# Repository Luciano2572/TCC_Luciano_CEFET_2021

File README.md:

# TCC_Luciano_CEFET_2021
Arquivos do projeto executado para o trabalho de conclusão de curso para o curso de engenharia eletrônica, Profa. Orientadora: Milena Faria Pinto, D.Sc.

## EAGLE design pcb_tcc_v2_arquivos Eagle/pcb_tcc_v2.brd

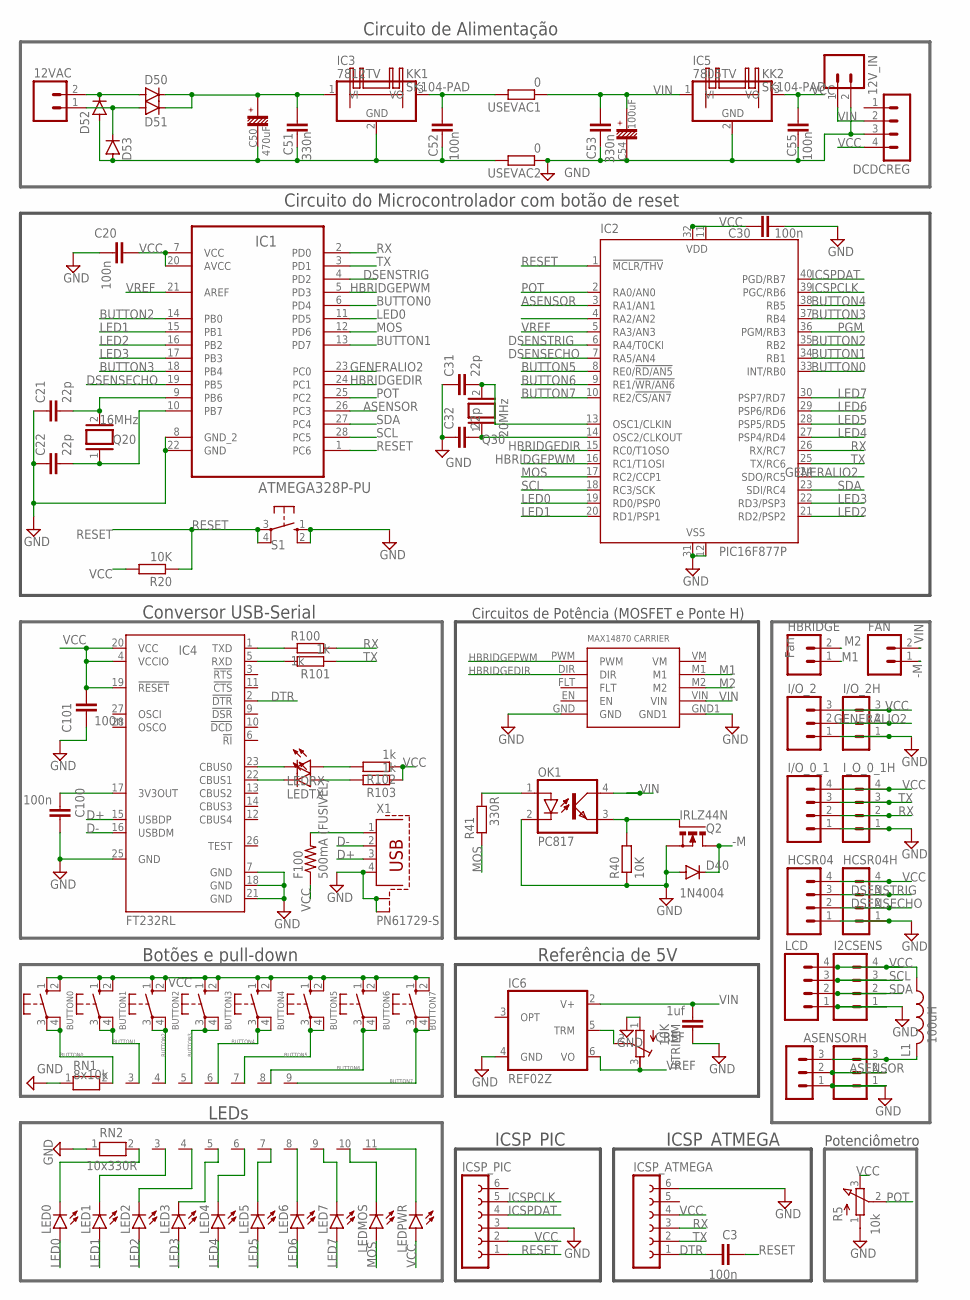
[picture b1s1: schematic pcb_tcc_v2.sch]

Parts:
12VAC, 12V_IN: M02; 02P
ASENSOR: M03; 03P
ASENSORH: MA03-1
BUTTON0, BUTTON1, BUTTON2, BUTTON3, BUTTON4, BUTTON5, BUTTON6, BUTTON7: 10-XX; B3F-10XX
C3, C20, C30, C52, C55, C100, C101: 100n; C5B2.5
C21, C22, C31, C32: 22p; C5B2.5
C50: 470uF; 16V-10-5.08
C51, C53: 330n; C5B2.5
C54: 100uF; 16V-6.3-2.54
CREF: 1uf; C2.5-2
D40, D50, D51, D52, D53: 1N4004; DO41-10
DCDCREG: MA04-1
F100: 500mA (FUSIVEL); R1206
FAN: M02; 02P
HBRIDGE: M02; 02P
HCSR04: M04; 04P
HCSR04H: MA04-1
I2CSENS: M04; 04P
I/O_0_1: M04; 04P
I/O_2: M03; 03P
I/O_2H: MA03-1
IC1: ATMEGA328P-PU; DIP254P762X457-28
IC2: PIC16F877P; DIL40
IC3: 7812TV; TO220V
IC4: FT232RL; SSOP28
IC5: 7805TV; TO220V
IC6: REF02Z; DIL08
ICSP_ATMEGA: FE06-1; FE06
ICSP_PIC: FE06-1; FE06
I_O_0_1H: MA04-1
KK1, KK2: SK104-PAD
L1: 100uH; 0204/7
LCD: M04; 04P
LED0, LED1, LED2, LED3, LED4, LED5, LED6, LED7: LED3MM
LEDMOS: LED3MM
LEDPWR: LED3MM
LEDRX: LED3MM
LEDTX: LED3MM
OK1: PC817; DIL04
Q2: IRLZ44N; TO220BV
Q20: 16MHz; QS
Q30: 20MHz; QS
R5: 10k; 3RP/1610N
R20, R40: 10K; 0207/10
R41: 330R; 0207/7
R100, R101, R102, R103: 1k; 0207/10
RN1: 8x10k; RN-9
RN2: 10x330R; RN-11
RTRIMM: 10K; RTRIM3296W
S1: 10-XX; B3F-10XX
U$1: MAX14870; POLOLU_CARRIER
USEVAC1, USEVAC2: 0; 0207/10
X1: PN61729-S

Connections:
-M: D40.C, FAN.1, Q2.D
ASENSOR: ASENSOR.2, ASENSORH.2, IC1.26 (PC3), IC2.3 (RA1/AN1)
BUTTON0: BUTTON0.3, BUTTON0.4 (P1), IC1.6 (PD4), IC2.33 (INT/RB0), RN1.2
BUTTON1: BUTTON1.3, BUTTON1.4 (P1), IC1.13 (PD7), IC2.34 (RB1), RN1.3
BUTTON2: BUTTON2.3, BUTTON2.4 (P1), IC1.14 (PB0), IC2.35 (RB2), RN1.4
BUTTON3: BUTTON3.3, BUTTON3.4 (P1), IC1.18 (PB4), IC2.37 (RB4), RN1.5
BUTTON4: BUTTON4.3, BUTTON4.4 (P1), IC2.38 (RB5), RN1.6
BUTTON5: BUTTON5.3, BUTTON5.4 (P1), IC2.8 (RE0/!RD/AN5), RN1.7
BUTTON6: BUTTON6.3, BUTTON6.4 (P1), IC2.9 (RE1/!WR/AN6), RN1.8
BUTTON7: BUTTON7.3, BUTTON7.4 (P1), IC2.10 (RE2/!CS/AN7), RN1.9
D+: IC4.15 (USBDP), X1.3
D-: IC4.16 (USBDM), X1.2
DSENSECHO: HCSR04.2, HCSR04H.2, IC1.19 (PB5), IC2.7 (RA5/AN4)
DSENSTRIG: HCSR04.3, HCSR04H.3, IC1.4 (PD2), IC2.6 (RA4/T0CKI)
DTR: C3.1, IC4.2 (!DTR), ICSP_ATMEGA.1
GENERALIO2: I/O_2.2, I/O_2H.2, IC1.23 (PC0), IC2.24 (SDO/RC5)
GND: 12V_IN.2, ASENSOR.1, ASENSORH.1, C20.2, C21.1, C22.1, C30.2, C31.1, C32.1, C53.1, C54.-, C55.1, C100.1, C101.2, CREF.1, D40.A, DCDCREG.3, HCSR04.1, HCSR04H.1, I2CSENS.1, I/O_0_1.1, I/O_2.1, I/O_2H.1, IC1.8 (GND_2), IC1.22 (GND), IC2.12 (VSS), IC2.31 (VSS), IC4.7 (GND), IC4.18 (GND), IC4.21 (GND), IC4.25 (GND), IC5.2 (GND), IC6.4 (GND), ICSP_ATMEGA.6, ICSP_PIC.3, I_O_0_1H.1, LCD.1, OK1.2 (C), Q2.S, R5.1 (A), R40.1, RN1.1, RN2.1, RTRIMM.1 (A), S1.1 (S), S1.2 (S1), U$1.GND, U$1.GND1, USEVAC2.1, X1.4, X1.S1, X1.S2
HBRIDGEDIR: IC1.24 (PC1), IC2.15 (RC0/T1OSO), U$1.DIR
HBRIDGEPWM: IC1.5 (PD3), IC2.16 (RC1/T1OSI), U$1.PWM
ICSPCLK: IC2.39 (PGC/RB6), ICSP_PIC.5
ICSPDAT: IC2.40 (PGD/RB7), ICSP_PIC.4
LED0: IC1.11 (PD5), IC2.19 (RD0/PSP0), LED0.A
LED1: IC1.15 (PB1), IC2.20 (RD1/PSP1), LED1.A
LED2: IC1.16 (PB2), IC2.21 (RD2/PSP2), LED2.A
LED3: IC1.17 (PB3), IC2.22 (RD3/PSP3), LED3.A
LED4: IC2.27 (PSP4/RD4), LED4.A
LED5: IC2.28 (PSP5/RD5), LED5.A
LED6: IC2.29 (PSP6/RD6), LED6.A
LED7: IC2.30 (PSP7/RD7), LED7.A
M1: HBRIDGE.1, U$1.M1
M2: HBRIDGE.2, U$1.M2
MOS: IC1.12 (PD6), IC2.17 (RC2/CCP1), LEDMOS.A, R41.1
unnamed: C21.2, IC1.9 (PB6), Q20.2
unnamed: C22.2, IC1.10 (PB7), Q20.1
unnamed: 12VAC.2, D50.A, D52.C
unnamed: OK1.3 (EMIT), Q2.G, R40.2
unnamed: 12VAC.1, D51.A, D53.C
unnamed: ASENSOR.3, ASENSORH.3, L1.2
unnamed: C50.-, C51.1, C52.1, D52.A, D53.A, IC3.2 (GND), USEVAC2.2
unnamed: OK1.1 (A), R41.2
unnamed: C50.+, C51.2, D50.C, D51.C, IC3.1 (VI)
unnamed: LED0.K (C), RN2.2
unnamed: C100.2, IC4.17 (3V3OUT)
unnamed: IC4.1 (TXD), R100.1
unnamed: IC4.5 (RXD), R101.2
unnamed: C52.2, IC3.3 (VO), USEVAC1.2
unnamed: LED1.K (C), RN2.3
unnamed: LED2.K (C), RN2.4
unnamed: LED3.K (C), RN2.5
unnamed: LED4.K (C), RN2.6
unnamed: LED5.K (C), RN2.7
unnamed: C31.2, IC2.13 (OSC1/CLKIN), Q30.2
unnamed: C32.2, IC2.14 (OSC2/CLKOUT), Q30.1
unnamed: LED6.K (C), RN2.8
unnamed: LED7.K (C), RN2.9
unnamed: LEDMOS.K (C), RN2.10
unnamed: IC6.5 (TRM), RTRIMM.2 (S)
unnamed: LEDPWR.K (C), RN2.11
unnamed: F100.2, X1.1
unnamed: IC4.23 (CBUS0), LEDRX.K (C)
unnamed: IC4.22 (CBUS1), LEDTX.K (C)
unnamed: LEDRX.A, R102.2
unnamed: LEDTX.A, R103.2
PGM: IC2.36 (PGM/RB3)
POT: IC1.25 (PC2), IC2.2 (RA0/AN0), R5.2 (S)
RESET: C3.2, IC1.1 (PC6), IC2.1 (!MCLR/THV), ICSP_PIC.1, R20.1, S1.3, S1.4 (P1)
RX: I/O_0_1.2, IC1.2 (PD0), IC2.26 (RX/RC7), ICSP_ATMEGA.3, I_O_0_1H.2, R100.2
SCL: I2CSENS.3, IC1.28 (PC5), IC2.18 (RC3/SCK), LCD.3
SDA: I2CSENS.2, IC1.27 (PC4), IC2.23 (SDI/RC4), LCD.2
TX: I/O_0_1.3, IC1.3 (PD1), IC2.25 (TX/RC6), ICSP_ATMEGA.2, I_O_0_1H.3, R101.1
VCC: BUTTON0.1 (S), BUTTON0.2 (S1), BUTTON1.1 (S), BUTTON1.2 (S1), BUTTON2.1 (S), BUTTON2.2 (S1), BUTTON3.1 (S), BUTTON3.2 (S1), BUTTON4.1 (S), BUTTON4.2 (S1), BUTTON5.1 (S), BUTTON5.2 (S1), BUTTON6.1 (S), BUTTON6.2 (S1), BUTTON7.1 (S), BUTTON7.2 (S1), C20.1, C30.1, C55.2, C101.1, DCDCREG.4, F100.1, HCSR04.4, HCSR04H.4, I2CSENS.4, I/O_0_1.4, I/O_2.3, I/O_2H.3, IC1.7 (VCC), IC1.20 (AVCC), IC2.11 (VDD), IC2.32 (VDD), IC4.4 (VCCIO), IC4.19 (!RESET), IC4.20 (VCC), IC5.3 (VO), ICSP_ATMEGA.4, ICSP_PIC.2, I_O_0_1H.4, L1.1, LCD.4, LEDPWR.A, R5.3 (E), R20.2, R102.1, R103.1
VIN: 12V_IN.1, C53.2, C54.+, CREF.2, DCDCREG.2, FAN.2, IC5.1 (VI), IC6.2 (V+), OK1.4 (COL), U$1.VIN, USEVAC1.1
VREF: IC1.21 (AREF), IC2.5 (RA3/AN3), IC6.6 (VO), RTRIMM.3 (E)

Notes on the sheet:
Fan
ICSP_PIC
ICSP_ATMEGA
Referência de 5V
Circuito do Microcontrolador com botão de reset
Conversor USB-Serial
Circuitos de Potência (MOSFET e Ponte H)
Botões e pull-down
LEDs
Potenciômetro
Circuito de Alimentação

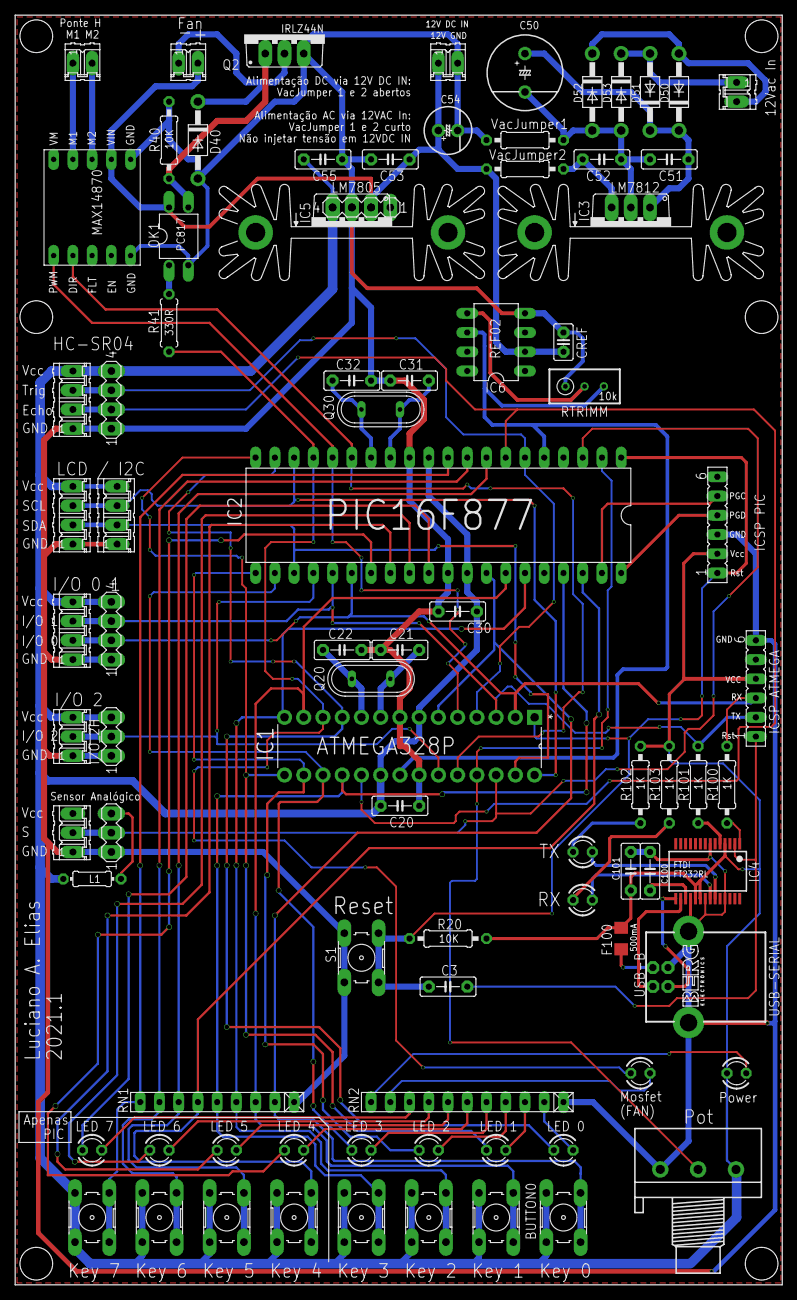
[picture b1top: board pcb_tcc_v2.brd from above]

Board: 2 copper layers, 101.3 x 167.6 mm, 88 parts (0 on the bottom side), 72 nets.

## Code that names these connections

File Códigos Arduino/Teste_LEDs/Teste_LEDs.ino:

#define io2 A0
#define hbridgedir A1
#define pot A2
#define asensor A3
//#define SDA A4
//#define SCL A5
#define io0 0
#define io1 1
#define dsenstrig 2
#define hbridgepwm 3
#define bot0 4
#define led0 5
#define mos 6
#define bot1 7
#define bot2 8
#define led1 9
#define led2 10
#define led3 11
#define bot3 12
#define dsensecho 13

void setup() {
  pinMode(bot0, INPUT);
  pinMode(bot1, INPUT);
  pinMode(bot2, INPUT);
  pinMode(bot3, INPUT);
  pinMode(pot, INPUT);
  pinMode(led0, OUTPUT);
  pinMode(led1, OUTPUT);
  pinMode(led2, OUTPUT);
  pinMode(led3, OUTPUT);
  pinMode(mos, OUTPUT);


// CONFIGURA A REFERÊNCIA DO ADC COMO EXTERNA
  // descomente a linha abaixo para utilizar a referência de tensão externa
  //analogReference(EXTERNAL);

  }

void loop() {
  
  piscaled();
  
  }

void piscaled(){
  digitalWrite(led3, LOW);
  digitalWrite(led0, HIGH);
  delay(500);
  digitalWrite(led0, LOW);
  digitalWrite(led1, HIGH);
  delay(500);
  digitalWrite(led1, LOW);
  digitalWrite(led2, HIGH);
  delay(500);
  digitalWrite(led2, LOW);
  digitalWrite(led3, HIGH);
  delay(500);  
  
  }

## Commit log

2021-02-06 Arquivos .stl e arquivos de produção da placa
2021-04-14 Arquivos de programação
